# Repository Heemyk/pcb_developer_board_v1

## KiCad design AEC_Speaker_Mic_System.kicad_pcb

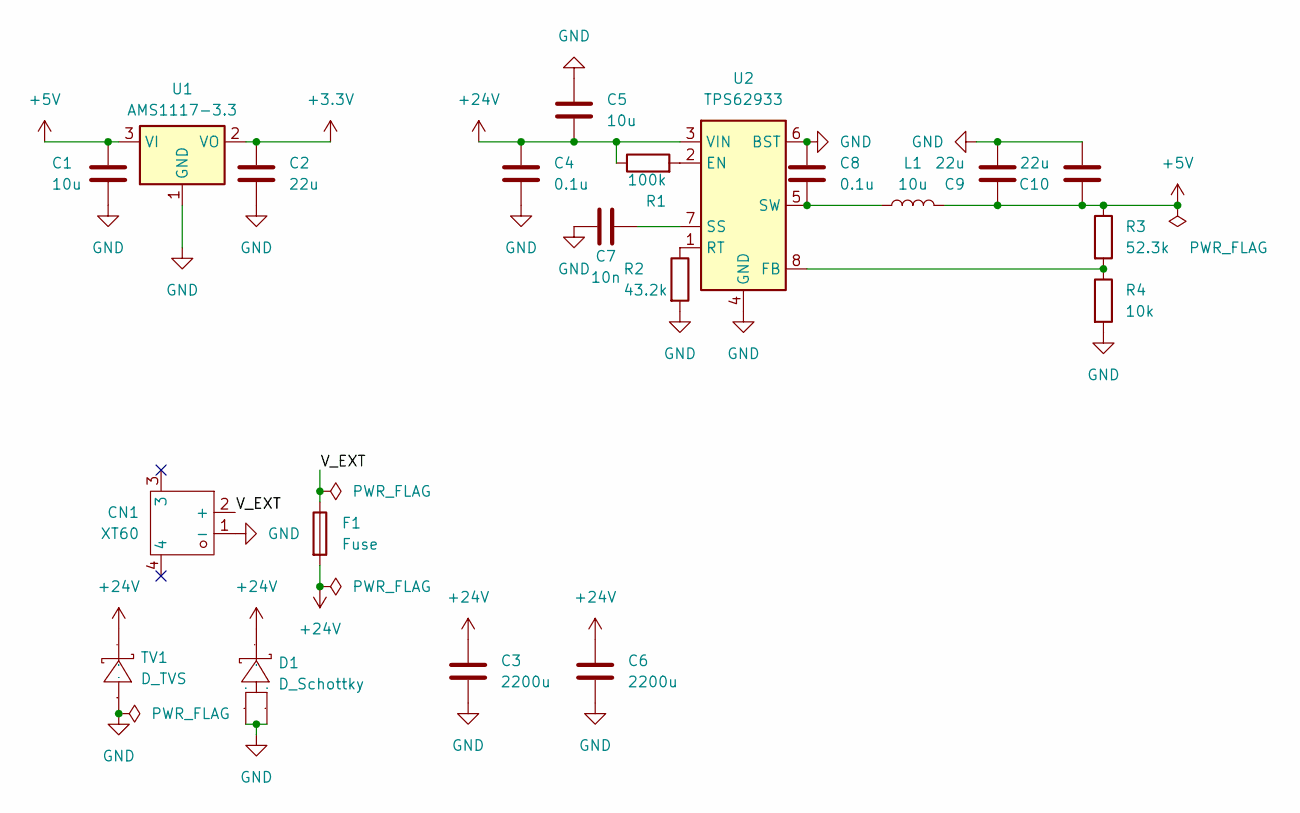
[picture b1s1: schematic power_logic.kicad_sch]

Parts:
C1: 10u; CP_EIA-3216-18_Kemet-A; Voltage Rating 16V; LCSC Part # C7171
C2: 22u; CP_EIA-3216-18_Kemet-A; Voltage Rating 6.6V; LCSC Part # C7183
C3, C6: 2200u; CAP-SMD_BD18.0-L19.0-W19.0-FD_EEEFK1E472SV; LCSC Part # C401728
C4, C8: 0.1u; C_0603_1608Metric; Voltage Rating 50V; LCSC Part # C14633
C5: 10u; C_1210_3225Metric; Voltage Rating 50V; LCSC Part # C116808
C7: 10n; C_0603_1608Metric; Voltage Rating 50V; LCSC Part # C1589
C9, C10: 22u; C_1206_3216Metric; Voltage Rating 25V; LCSC Part # C12891
CN1: XT60; CONN-TH_XT60PW-M; Manufacturer Part XT60PW-M; LCSC Part Name AMASS(艾迈斯)航模插头xt60连接器150公母对接pw锂电池公头 板插卧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
D1: D_Schottky; TO-277_3P-L5.4-W4.0-LS6.5-BR; Manufacturer Part SL1545; LCSC Part Name 电压:45V 电流:15A
F1: Fuse; F1206_32V_12A; LCSC Part # C126815
L1: 10u; IND-SMD_L10.4-W10.3; LCSC Part # C9935
R1: 100k; R_0603_1608Metric
R2: 43.2k; R_0603_1608Metric; LCSC Part # C22356315
R3: 52.3k; R_0603_1608Metric; LCSC Part # C22369875
R4: 10k; R_0603_1608Metric
TV1: D_TVS; Diode_SMC_L7.1-W6.2-LS8.1-R-RD; Manufacturer Part SMCJ28A; LCSC Part Name 单向TVS 28V截止 峰值浪涌电流：33.1A@10/1000us
U1: AMS1117-3.3; SOT-223-3_TabPin2; LCSC Part # C6186
U2: TPS62933; SOT-583-8; LCSC Part # C5219272

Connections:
+3.3V: C2.2, U1.2 (VO); also elsewhere on the board
+5V: C1.2, C9.1, C10.1, L1.2, R3.1, U1.3 (VI); also elsewhere on the board
+24V: C3.1, C4.1, C5.2, C6.1, D1.2 (K), F1.2, R1.1, TV1.2 (K), U2.3 (VIN); also elsewhere on the board
/PCB_Power/V_EXT: CN1.2 (+), F1.1
GND: C1.1, C2.1, C3.2, C4.2, C5.1, C6.2, C7.1, C8.1, C9.2, C10.2, CN1.1 (-), D1.1 (A), D1.3 (A), R2.2, R4.2, TV1.1 (A), U1.1 (GND), U2.4 (GND), U2.6 (BST); also elsewhere on the board
unnamed: R1.2, U2.2 (EN)
unnamed: R3.2, R4.1, U2.8 (FB)
unnamed: R2.1, U2.1 (RT)
unnamed: C7.2, U2.7 (SS)
unnamed: C8.2, L1.1, U2.5 (SW)

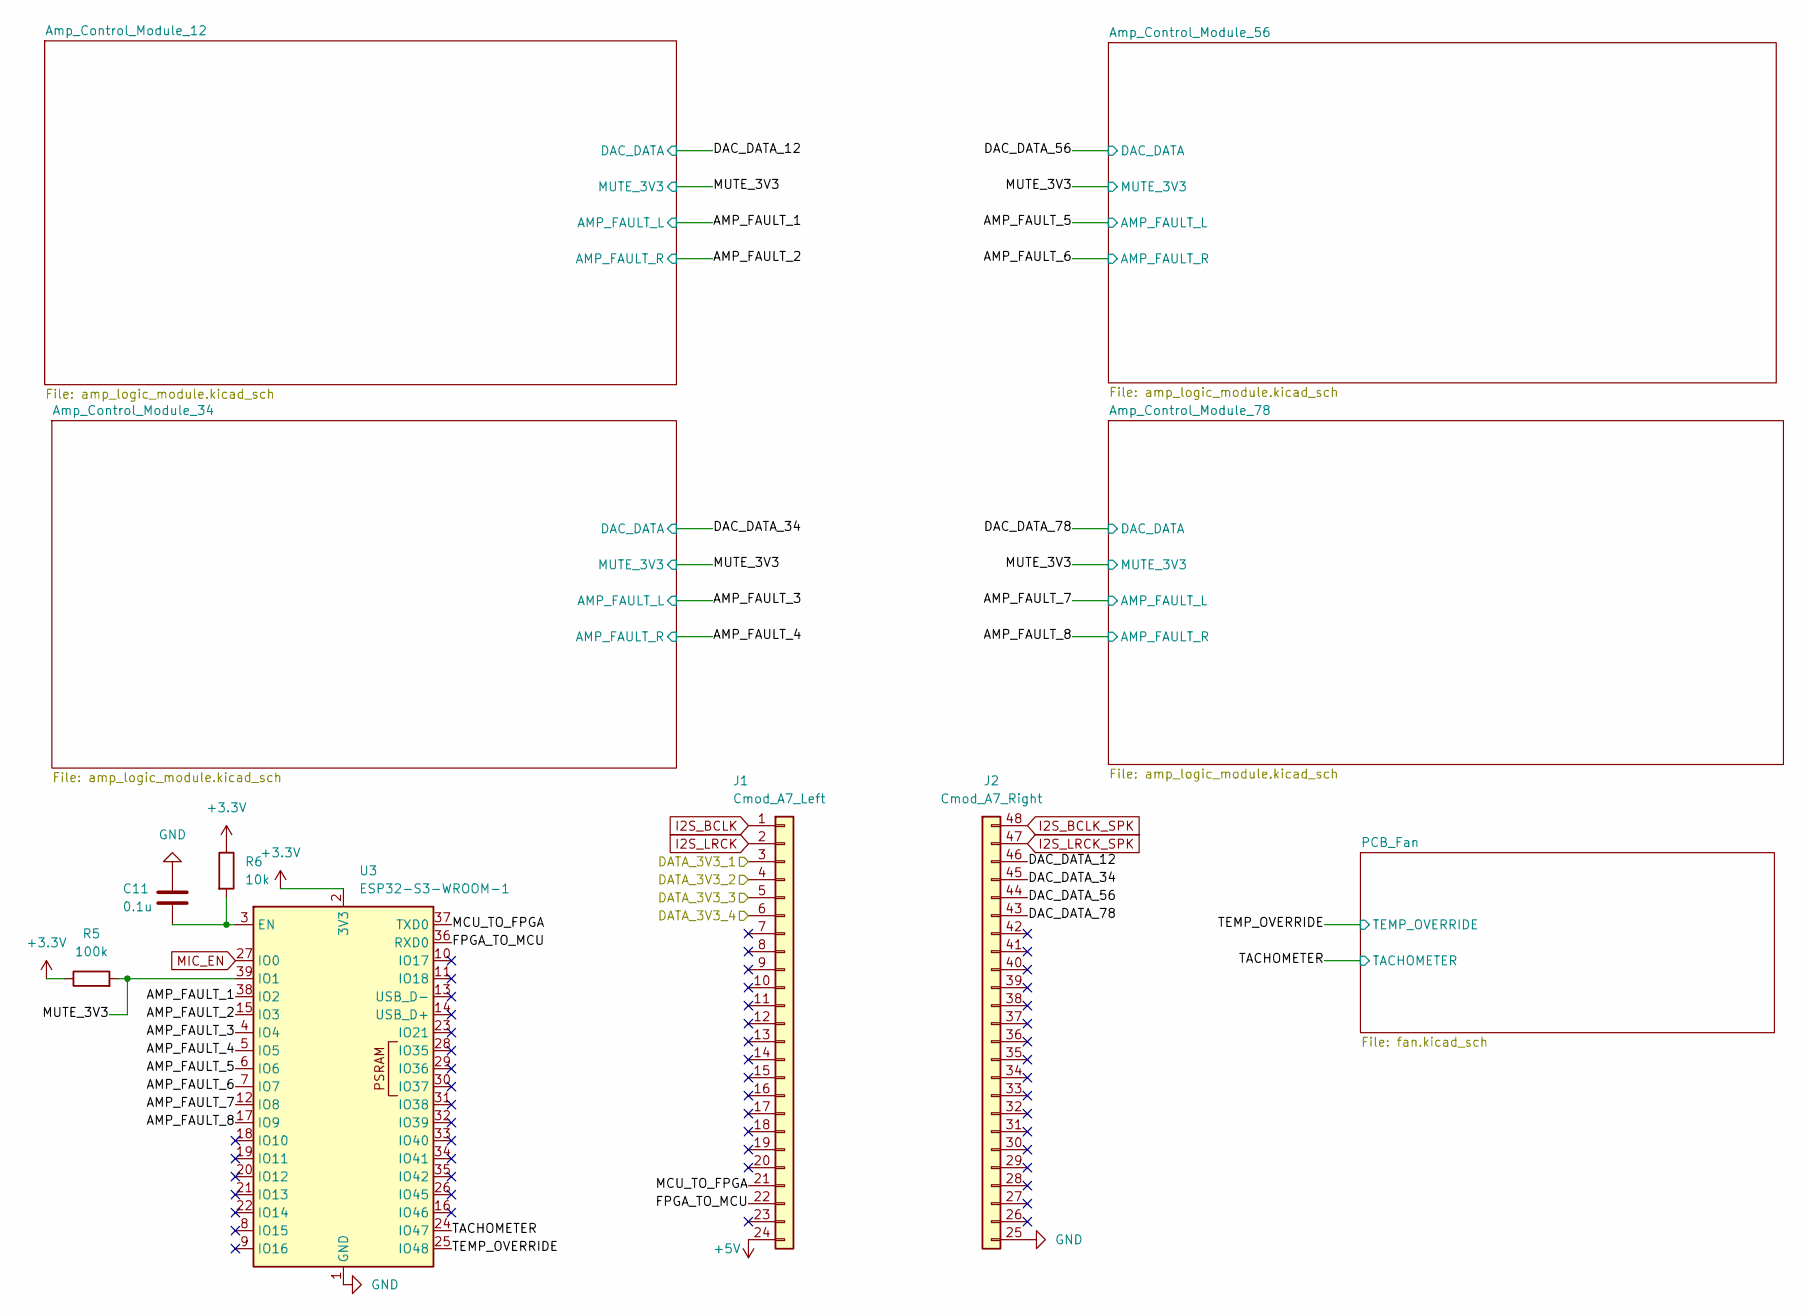
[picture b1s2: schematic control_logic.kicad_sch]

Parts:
C11: 0.1u; C_0603_1608Metric
J1: Cmod_A7_Left; HDR-TH_24P-P2.54-V-F; LCSC Part # C41376163
J2: Cmod_A7_Right; HDR-TH_24P-P2.54-V-F-RIGHT_SIDE_NUMBERING; LCSC Part # C41376163
R5: 100k; R_0603_1608Metric
R6: 10k; R_0603_1608Metric
U3: ESP32-S3-WROOM-1; LCSC Part # C2913202

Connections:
+3.3V: R5.1, R6.1, U3.2 (3V3); also elsewhere on the board
+5V: J1.24; also elsewhere on the board
/Hub_Main/DATA_3V3_1: J1.3; also elsewhere on the board
/Hub_Main/DATA_3V3_2: J1.4; also elsewhere on the board
/Hub_Main/DATA_3V3_3: J1.5; also elsewhere on the board
/Hub_Main/DATA_3V3_4: J1.6; also elsewhere on the board
/PCB_Control/AMP_FAULT_1: U3.38 (IO2); also elsewhere on the board
/PCB_Control/AMP_FAULT_2: U3.15 (IO3); also elsewhere on the board
/PCB_Control/AMP_FAULT_3: U3.4 (IO4); also elsewhere on the board
/PCB_Control/AMP_FAULT_4: U3.5 (IO5); also elsewhere on the board
/PCB_Control/AMP_FAULT_5: U3.6 (IO6); also elsewhere on the board
/PCB_Control/AMP_FAULT_6: U3.7 (IO7); also elsewhere on the board
/PCB_Control/AMP_FAULT_7: U3.12 (IO8); also elsewhere on the board
/PCB_Control/AMP_FAULT_8: U3.17 (IO9); also elsewhere on the board
/PCB_Control/DAC_DATA_12: J2.46 (Pin_22); also elsewhere on the board
/PCB_Control/DAC_DATA_34: J2.45 (Pin_21); also elsewhere on the board
/PCB_Control/DAC_DATA_56: J2.44 (Pin_20); also elsewhere on the board
/PCB_Control/DAC_DATA_78: J2.43 (Pin_19); also elsewhere on the board
/PCB_Control/FPGA_TO_MCU: J1.22, U3.36 (RXD0)
/PCB_Control/MCU_TO_FPGA: J1.21, U3.37 (TXD0)
/PCB_Control/MUTE_3V3: R5.2, U3.39 (IO1); also elsewhere on the board
/PCB_Control/TACHOMETER: U3.24 (IO47); also elsewhere on the board
/PCB_Control/TEMP_OVERRIDE: U3.25 (IO48); also elsewhere on the board
GND: C11.1, J2.25 (Pin_1), U3.1 (GND), U3.40 (GND), U3.41 (GND); also elsewhere on the board
I2S_BCLK: J1.1; also elsewhere on the board
I2S_BCLK_SPK: J2.48 (Pin_24); also elsewhere on the board
I2S_LRCK: J1.2; also elsewhere on the board
I2S_LRCK_SPK: J2.47 (Pin_23); also elsewhere on the board
MIC_EN: U3.27 (IO0); also elsewhere on the board
unnamed: C11.2, R6.2, U3.3 (EN)

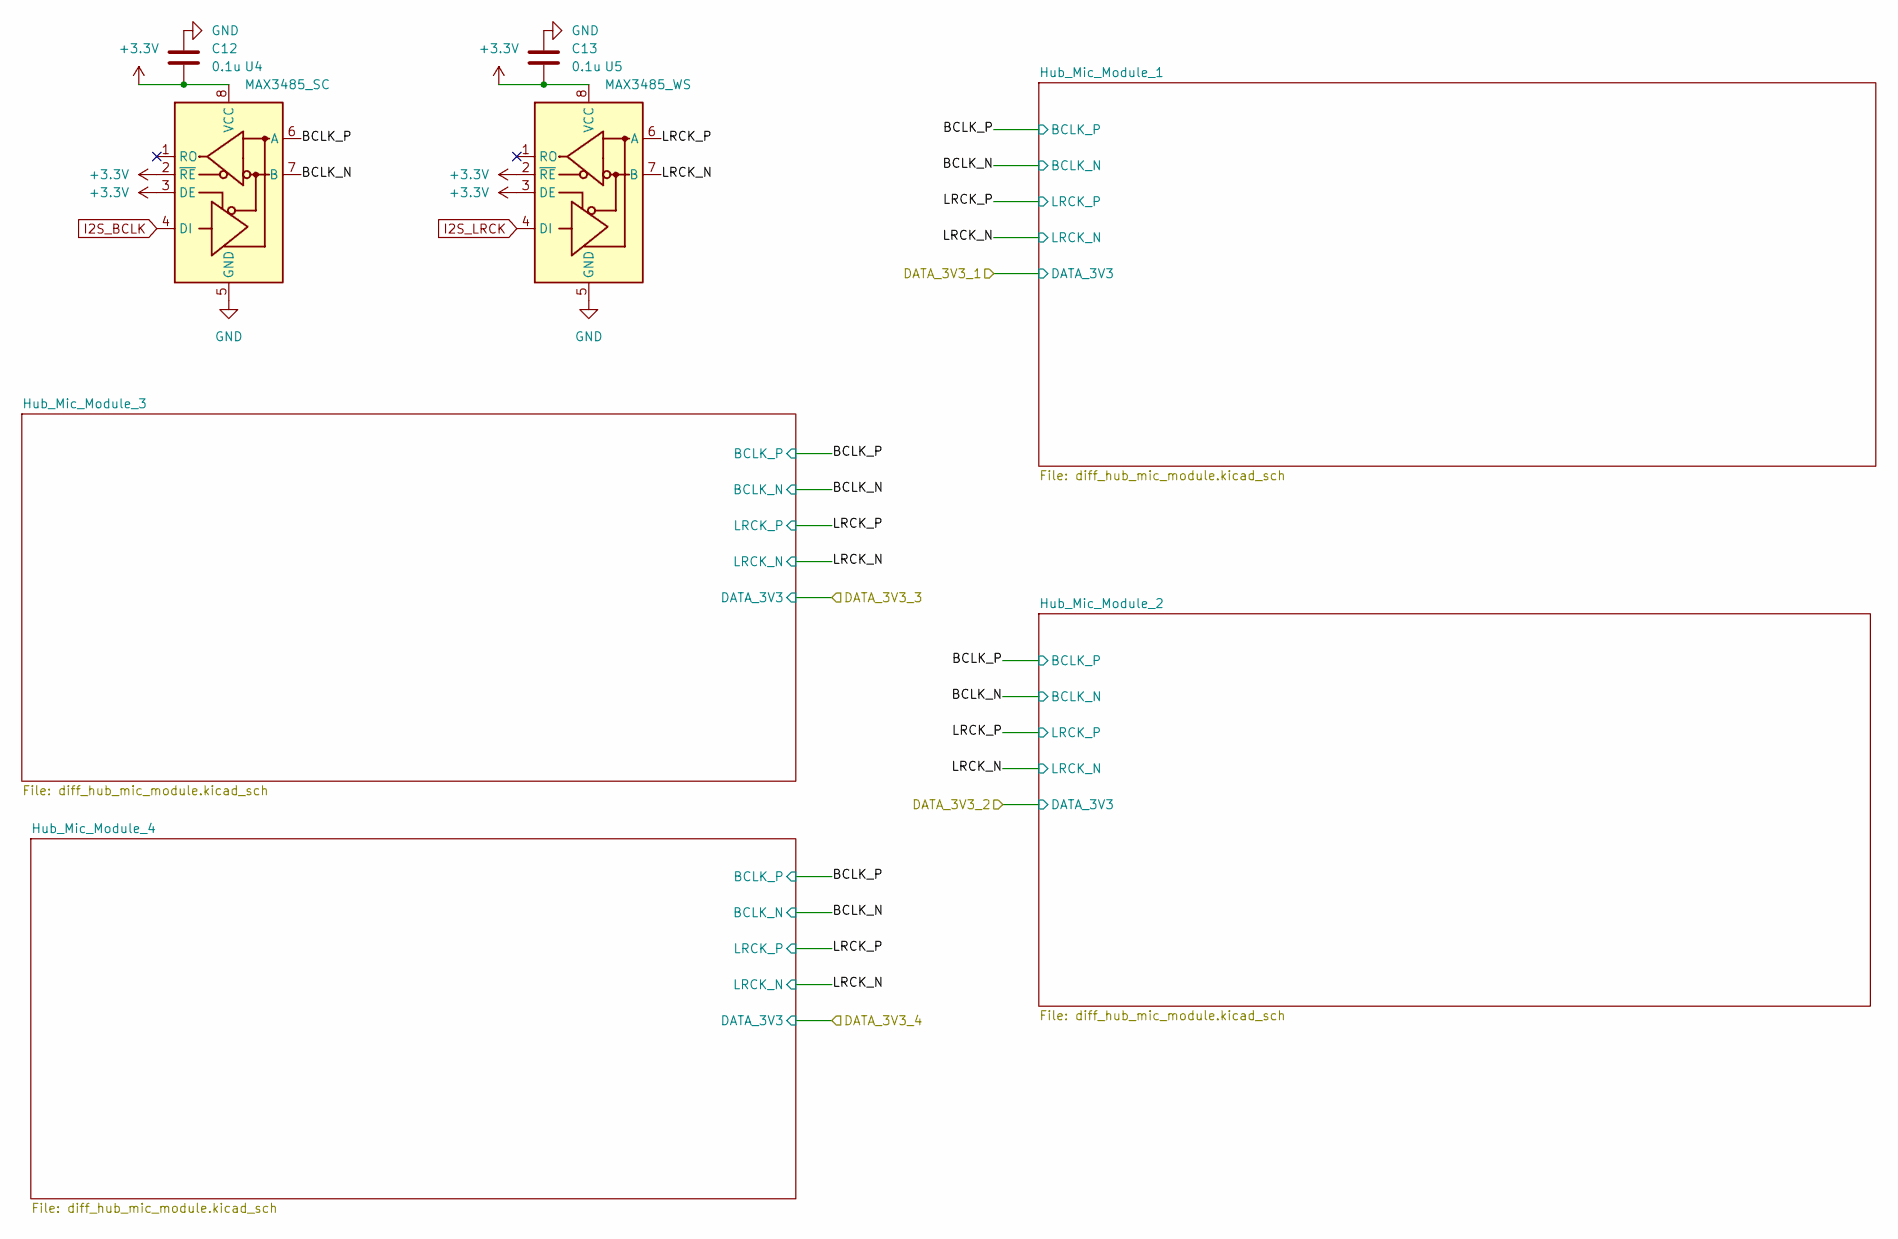
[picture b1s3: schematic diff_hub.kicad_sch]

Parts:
C12, C13: 0.1u; C_0603_1608Metric
U4: MAX3485_SC; SOIC-8_3.9x4.9mm_P1.27mm
U5: MAX3485_WS; SOIC-8_3.9x4.9mm_P1.27mm

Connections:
+3.3V: C12.2, C13.2, U4.2 (~RE), U4.3 (DE), U4.8 (VCC), U5.2 (~RE), U5.3 (DE), U5.8 (VCC); also elsewhere on the board
/Hub_Main/BCLK_N: U4.7 (B); also elsewhere on the board
/Hub_Main/BCLK_P: U4.6 (A); also elsewhere on the board
/Hub_Main/LRCK_N: U5.7 (B); also elsewhere on the board
/Hub_Main/LRCK_P: U5.6 (A); also elsewhere on the board
GND: C12.1, C13.1, U4.5 (GND), U5.5 (GND); also elsewhere on the board
I2S_BCLK: U4.4 (DI); also elsewhere on the board
I2S_LRCK: U5.4 (DI); also elsewhere on the board

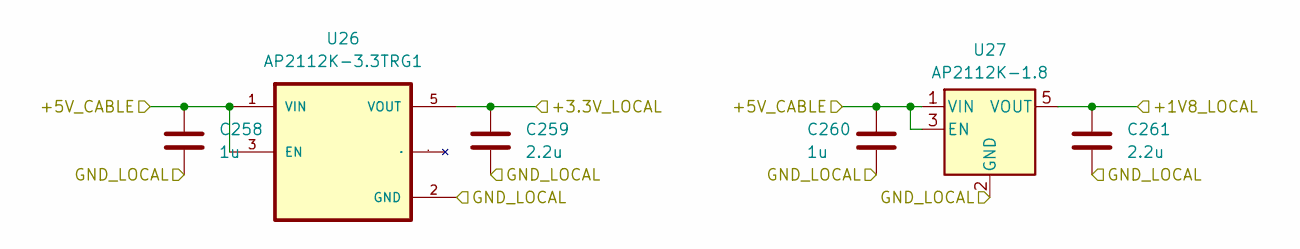
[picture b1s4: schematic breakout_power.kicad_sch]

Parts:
C258: 1u; C_0603_1608Metric; LCSC Part # C15849
C259, C261: 2.2u; C_0603_1608Metric; LCSC Part # C23630
C260: 1u; IND-SMD_L10.4-W10.3; LCSC Part # C15849
U26: AP2112K-3.3TRG1; SOT95P285X140-5N; PARTREV 2-2
U27: AP2112K-1.8; SOT-23-5

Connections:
/Breakout_1/+1V8_LOCAL: C261.2, U27.5 (VOUT); also elsewhere on the board
/Breakout_1/+3.3V_LOCAL: C259.2, U26.5 (VOUT); also elsewhere on the board
/Breakout_1/+5V_CABLE: C258.1, C260.1, U26.1 (VIN), U26.3 (EN), U27.1 (VIN), U27.3 (EN); also elsewhere on the board
/Breakout_1/GND_LOCAL: C258.2, C259.1, C260.2, C261.1, U26.2 (GND), U27.2 (GND); also elsewhere on the board

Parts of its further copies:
C265, C274, C282, C293, C301: 1u; C_0603_1608Metric; LCSC Part # C15849
C266, C268, C275, C277, C283, C285, C294, C296, C302, C304: 2.2u; C_0603_1608Metric; LCSC Part # C23630
C267, C276, C284, C295, C303: 1u; IND-SMD_L10.4-W10.3; LCSC Part # C15849
U29, U40, U47, U55, U62: AP2112K-3.3TRG1; SOT95P285X140-5N; PARTREV 2-2
U30, U41, U48, U56, U63: AP2112K-1.8; SOT-23-5

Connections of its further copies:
/Breakout_2/+1V8_LOCAL: C277.2, U41.5 (VOUT); also elsewhere on the board
/Breakout_2/+3.3V_LOCAL: C275.2, U40.5 (VOUT); also elsewhere on the board
/Breakout_2/+5V_CABLE: C274.1, C276.1, U40.1 (VIN), U40.3 (EN), U41.1 (VIN), U41.3 (EN); also elsewhere on the board
/Breakout_2/GND_LOCAL: C274.2, C275.1, C276.2, C277.1, U40.2 (GND), U41.2 (GND); also elsewhere on the board
/Breakout_3/+1V8_LOCAL: C296.2, U56.5 (VOUT); also elsewhere on the board
/Breakout_3/+3.3V_LOCAL: C294.2, U55.5 (VOUT); also elsewhere on the board
/Breakout_3/+5V_CABLE: C293.1, C295.1, U55.1 (VIN), U55.3 (EN), U56.1 (VIN), U56.3 (EN); also elsewhere on the board
/Breakout_3/GND_LOCAL: C293.2, C294.1, C295.2, C296.1, U55.2 (GND), U56.2 (GND); also elsewhere on the board
/Breakout_4/+1V8_LOCAL: C268.2, U30.5 (VOUT); also elsewhere on the board
/Breakout_4/+3.3V_LOCAL: C266.2, U29.5 (VOUT); also elsewhere on the board
/Breakout_4/+5V_CABLE: C265.1, C267.1, U29.1 (VIN), U29.3 (EN), U30.1 (VIN), U30.3 (EN); also elsewhere on the board
/Breakout_4/GND_LOCAL: C265.2, C266.1, C267.2, C268.1, U29.2 (GND), U30.2 (GND); also elsewhere on the board
/Breakout_5/+1V8_LOCAL: C285.2, U48.5 (VOUT); also elsewhere on the board
/Breakout_5/+3.3V_LOCAL: C283.2, U47.5 (VOUT); also elsewhere on the board
/Breakout_5/+5V_CABLE: C282.1, C284.1, U47.1 (VIN), U47.3 (EN), U48.1 (VIN), U48.3 (EN); also elsewhere on the board
/Breakout_5/GND_LOCAL: C282.2, C283.1, C284.2, C285.1, U47.2 (GND), U48.2 (GND); also elsewhere on the board
/Breakout_6/+1V8_LOCAL: C304.2, U63.5 (VOUT); also elsewhere on the board
/Breakout_6/+3.3V_LOCAL: C302.2, U62.5 (VOUT); also elsewhere on the board
/Breakout_6/+5V_CABLE: C301.1, C303.1, U62.1 (VIN), U62.3 (EN), U63.1 (VIN), U63.3 (EN); also elsewhere on the board
/Breakout_6/GND_LOCAL: C301.2, C302.1, C303.2, C304.1, U62.2 (GND), U63.2 (GND); also elsewhere on the board

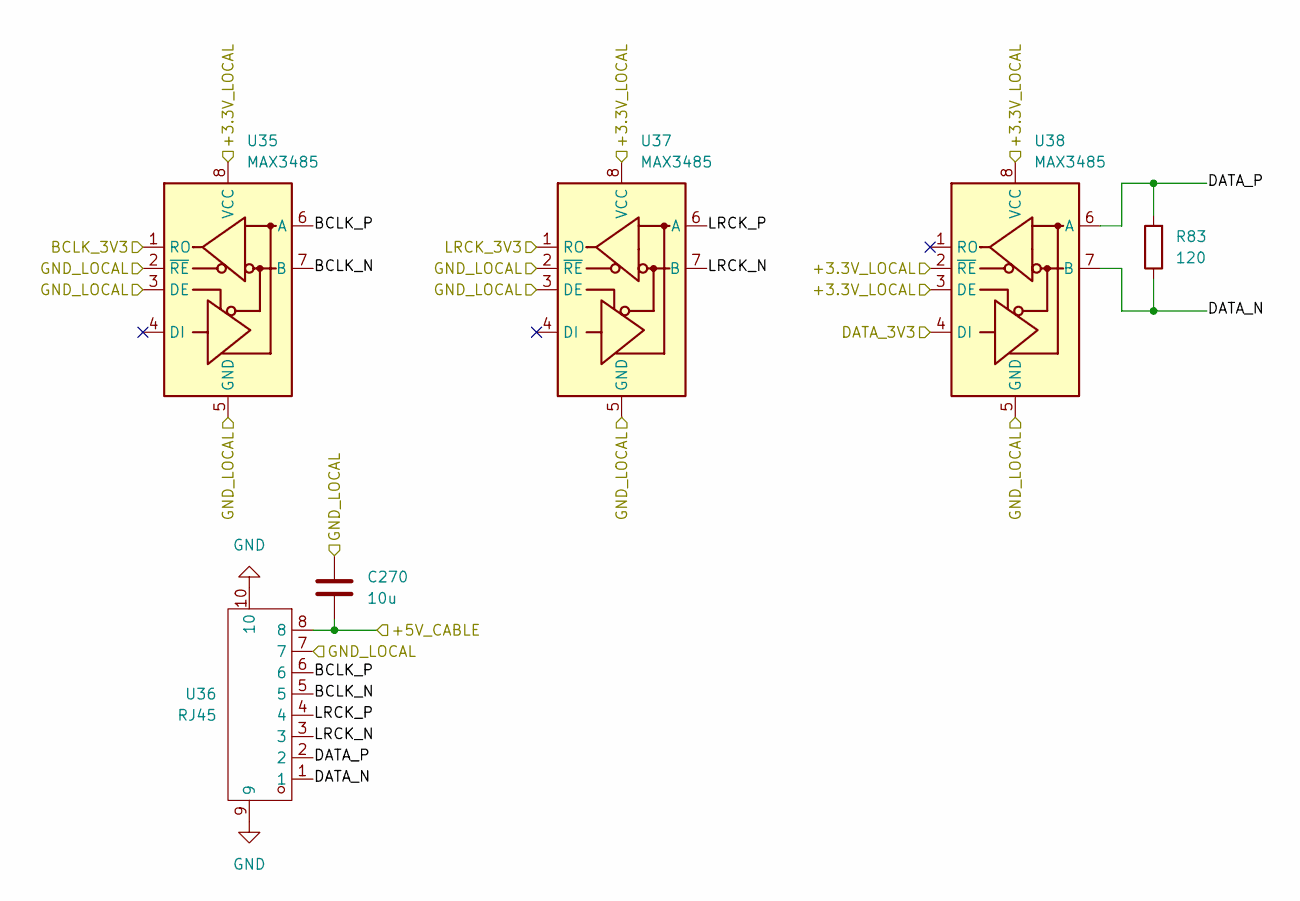
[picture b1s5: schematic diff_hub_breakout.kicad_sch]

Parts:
C270: 10u; C_0603_1608Metric
R83: 120; R_0603_1608Metric
U35, U37, U38: MAX3485; SOIC-8_3.9x4.9mm_P1.27mm
U36: RJ45; RJ45-SMD_HC-RJ45-055-4_2; Manufacturer Part HC-RJ45-055-4; LCSC Part Name 沉板 不带LED

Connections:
/Breakout_1/+3.3V_LOCAL: U35.8 (VCC), U37.8 (VCC), U38.2 (~RE), U38.3 (DE), U38.8 (VCC); also elsewhere on the board
/Breakout_1/+5V_CABLE: C270.2, U36.8; also elsewhere on the board
/Breakout_1/Breakout_Control/BCLK_3V3: U35.1 (RO); also elsewhere on the board
/Breakout_1/Breakout_Control/DATA_3V3: U38.4 (DI); also elsewhere on the board
/Breakout_1/Breakout_Control/WS_3V3: U37.1 (RO); also elsewhere on the board
/Breakout_1/Breakout_Hub/BCLK_N: U35.7 (B), U36.5
/Breakout_1/Breakout_Hub/BCLK_P: U35.6 (A), U36.6
/Breakout_1/Breakout_Hub/DATA_N: R83.1, U36.1, U38.7 (B)
/Breakout_1/Breakout_Hub/DATA_P: R83.2, U36.2, U38.6 (A)
/Breakout_1/Breakout_Hub/LRCK_N: U36.3, U37.7 (B)
/Breakout_1/Breakout_Hub/LRCK_P: U36.4, U37.6 (A)
/Breakout_1/GND_LOCAL: C270.1, U35.2 (~RE), U35.3 (DE), U35.5 (GND), U36.7, U37.2 (~RE), U37.3 (DE), U37.5 (GND), U38.5 (GND); also elsewhere on the board
GND: U36.9, U36.10; also elsewhere on the board

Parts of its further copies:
C269, C278, C286, C297, C305: 10u; C_0603_1608Metric
R81, R85, R88, R93, R101: 120; R_0603_1608Metric
U31, U33, U34, U42, U44, U45, U49, U51, U52, U57, U59, U60, U64, U67, U68: MAX3485; SOIC-8_3.9x4.9mm_P1.27mm
U32, U43, U50, U58, U65: RJ45; RJ45-SMD_HC-RJ45-055-4_2; Manufacturer Part HC-RJ45-055-4; LCSC Part Name 沉板 不带LED

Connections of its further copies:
/Breakout_2/+3.3V_LOCAL: U42.8 (VCC), U44.8 (VCC), U45.2 (~RE), U45.3 (DE), U45.8 (VCC); also elsewhere on the board
/Breakout_2/+5V_CABLE: C278.2, U43.8; also elsewhere on the board
/Breakout_2/Breakout_Control/BCLK_3V3: U42.1 (RO); also elsewhere on the board
/Breakout_2/Breakout_Control/DATA_3V3: U45.4 (DI); also elsewhere on the board
/Breakout_2/Breakout_Control/WS_3V3: U44.1 (RO); also elsewhere on the board
/Breakout_2/Breakout_Hub/BCLK_N: U42.7 (B), U43.5
/Breakout_2/Breakout_Hub/BCLK_P: U42.6 (A), U43.6
/Breakout_2/Breakout_Hub/DATA_N: R85.1, U43.1, U45.7 (B)
/Breakout_2/Breakout_Hub/DATA_P: R85.2, U43.2, U45.6 (A)
/Breakout_2/Breakout_Hub/LRCK_N: U43.3, U44.7 (B)
/Breakout_2/Breakout_Hub/LRCK_P: U43.4, U44.6 (A)
/Breakout_2/GND_LOCAL: C278.1, U42.2 (~RE), U42.3 (DE), U42.5 (GND), U43.7, U44.2 (~RE), U44.3 (DE), U44.5 (GND), U45.5 (GND); also elsewhere on the board
/Breakout_3/+3.3V_LOCAL: U57.8 (VCC), U59.8 (VCC), U60.2 (~RE), U60.3 (DE), U60.8 (VCC); also elsewhere on the board
/Breakout_3/+5V_CABLE: C297.2, U58.8; also elsewhere on the board
/Breakout_3/Breakout_Control/BCLK_3V3: U57.1 (RO); also elsewhere on the board
/Breakout_3/Breakout_Control/DATA_3V3: U60.4 (DI); also elsewhere on the board
/Breakout_3/Breakout_Control/WS_3V3: U59.1 (RO); also elsewhere on the board
/Breakout_3/Breakout_Hub/BCLK_N: U57.7 (B), U58.5
/Breakout_3/Breakout_Hub/BCLK_P: U57.6 (A), U58.6
/Breakout_3/Breakout_Hub/DATA_N: R93.1, U58.1, U60.7 (B)
/Breakout_3/Breakout_Hub/DATA_P: R93.2, U58.2, U60.6 (A)
/Breakout_3/Breakout_Hub/LRCK_N: U58.3, U59.7 (B)
/Breakout_3/Breakout_Hub/LRCK_P: U58.4, U59.6 (A)
/Breakout_3/GND_LOCAL: C297.1, U57.2 (~RE), U57.3 (DE), U57.5 (GND), U58.7, U59.2 (~RE), U59.3 (DE), U59.5 (GND), U60.5 (GND); also elsewhere on the board
/Breakout_4/+3.3V_LOCAL: U31.8 (VCC), U33.8 (VCC), U34.2 (~RE), U34.3 (DE), U34.8 (VCC); also elsewhere on the board
/Breakout_4/+5V_CABLE: C269.2, U32.8; also elsewhere on the board
/Breakout_4/Breakout_Control/BCLK_3V3: U31.1 (RO); also elsewhere on the board
/Breakout_4/Breakout_Control/DATA_3V3: U34.4 (DI); also elsewhere on the board
/Breakout_4/Breakout_Control/WS_3V3: U33.1 (RO); also elsewhere on the board
/Breakout_4/Breakout_Hub/BCLK_N: U31.7 (B), U32.5
/Breakout_4/Breakout_Hub/BCLK_P: U31.6 (A), U32.6
/Breakout_4/Breakout_Hub/DATA_N: R81.1, U32.1, U34.7 (B)
/Breakout_4/Breakout_Hub/DATA_P: R81.2, U32.2, U34.6 (A)
/Breakout_4/Breakout_Hub/LRCK_N: U32.3, U33.7 (B)
/Breakout_4/Breakout_Hub/LRCK_P: U32.4, U33.6 (A)
/Breakout_4/GND_LOCAL: C269.1, U31.2 (~RE), U31.3 (DE), U31.5 (GND), U32.7, U33.2 (~RE), U33.3 (DE), U33.5 (GND), U34.5 (GND); also elsewhere on the board
/Breakout_5/+3.3V_LOCAL: U49.8 (VCC), U51.8 (VCC), U52.2 (~RE), U52.3 (DE), U52.8 (VCC); also elsewhere on the board
/Breakout_5/+5V_CABLE: C286.2, U50.8; also elsewhere on the board
/Breakout_5/Breakout_Control/BCLK_3V3: U49.1 (RO); also elsewhere on the board
/Breakout_5/Breakout_Control/DATA_3V3: U52.4 (DI); also elsewhere on the board
/Breakout_5/Breakout_Control/WS_3V3: U51.1 (RO); also elsewhere on the board
/Breakout_5/Breakout_Hub/BCLK_N: U49.7 (B), U50.5
/Breakout_5/Breakout_Hub/BCLK_P: U49.6 (A), U50.6
/Breakout_5/Breakout_Hub/DATA_N: R88.1, U50.1, U52.7 (B)
/Breakout_5/Breakout_Hub/DATA_P: R88.2, U50.2, U52.6 (A)
/Breakout_5/Breakout_Hub/LRCK_N: U50.3, U51.7 (B)
/Breakout_5/Breakout_Hub/LRCK_P: U50.4, U51.6 (A)
/Breakout_5/GND_LOCAL: C286.1, U49.2 (~RE), U49.3 (DE), U49.5 (GND), U50.7, U51.2 (~RE), U51.3 (DE), U51.5 (GND), U52.5 (GND); also elsewhere on the board
/Breakout_6/+3.3V_LOCAL: U64.8 (VCC), U67.8 (VCC), U68.2 (~RE), U68.3 (DE), U68.8 (VCC); also elsewhere on the board
/Breakout_6/+5V_CABLE: C305.2, U65.8; also elsewhere on the board
/Breakout_6/Breakout_Control/BCLK_3V3: U64.1 (RO); also elsewhere on the board
/Breakout_6/Breakout_Control/DATA_3V3: U68.4 (DI); also elsewhere on the board
/Breakout_6/Breakout_Control/WS_3V3: U67.1 (RO); also elsewhere on the board
/Breakout_6/Breakout_Hub/BCLK_N: U64.7 (B), U65.5
/Breakout_6/Breakout_Hub/BCLK_P: U64.6 (A), U65.6
/Breakout_6/Breakout_Hub/DATA_N: R101.1, U65.1, U68.7 (B)
/Breakout_6/Breakout_Hub/DATA_P: R101.2, U65.2, U68.6 (A)
/Breakout_6/Breakout_Hub/LRCK_N: U65.3, U67.7 (B)
/Breakout_6/Breakout_Hub/LRCK_P: U65.4, U67.6 (A)
/Breakout_6/GND_LOCAL: C305.1, U64.2 (~RE), U64.3 (DE), U64.5 (GND), U65.7, U67.2 (~RE), U67.3 (DE), U67.5 (GND), U68.5 (GND); also elsewhere on the board
GND: U32.9, U32.10, U43.9, U43.10, U50.9, U50.10, U58.9, U58.10, U65.9, U65.10; also elsewhere on the board

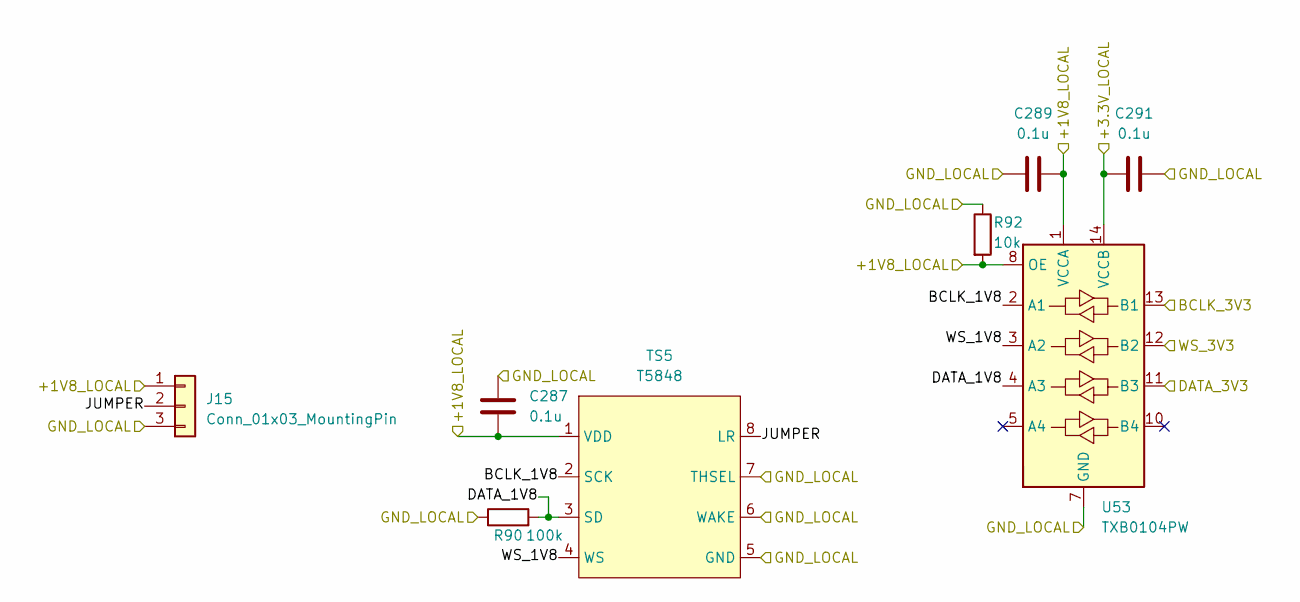
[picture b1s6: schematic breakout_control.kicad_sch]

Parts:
C287, C289, C291: 0.1u; C_0603_1608Metric
J15: Conn_01x03_MountingPin; PinHeader_1x03_P2.54mm_Vertical_SMD_Pin1Left; LCSC Part # C5160786
R90: 100k; R_0603_1608Metric
R92: 10k; R_0603_1608Metric
TS5: T5848; TDK_T5848_Pad
U53: TXB0104PW; TSSOP-14_4.4x5mm_P0.65mm

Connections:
/Breakout_1/+1V8_LOCAL: C287.1, C289.2, J15.1, R92.2, TS5.1 (VDD), U53.1 (VCCA), U53.8 (OE); also elsewhere on the board
/Breakout_1/+3.3V_LOCAL: C291.1, U53.14 (VCCB); also elsewhere on the board
/Breakout_1/Breakout_Control/BCLK_1V8: TS5.2 (SCK), U53.2 (A1)
/Breakout_1/Breakout_Control/BCLK_3V3: U53.13 (B1); also elsewhere on the board
/Breakout_1/Breakout_Control/DATA_1V8: R90.2, TS5.3 (SD), U53.4 (A3)
/Breakout_1/Breakout_Control/DATA_3V3: U53.11 (B3); also elsewhere on the board
/Breakout_1/Breakout_Control/JUMPER: J15.2, TS5.8 (LR)
/Breakout_1/Breakout_Control/WS_1V8: TS5.4 (WS), U53.3 (A2)
/Breakout_1/Breakout_Control/WS_3V3: U53.12 (B2); also elsewhere on the board
/Breakout_1/GND_LOCAL: C287.2, C289.1, C291.2, J15.3, R90.1, R92.1, TS5.5 (GND), TS5.6 (WAKE), TS5.7 (THSEL), U53.7 (GND); also elsewhere on the board

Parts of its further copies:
C262, C263, C264, C271, C272, C273, C279, C280, C281, C288, C290, C292, C298, C299, C300: 0.1u; C_0603_1608Metric
J11, J12, J13, J14, J16: Conn_01x03_MountingPin; PinHeader_1x03_P2.54mm_Vertical_SMD_Pin1Left; LCSC Part # C5160786
R79, R82, R86, R89, R94: 100k; R_0603_1608Metric
R80, R84, R87, R91, R95: 10k; R_0603_1608Metric
TS1, TS2, TS3, TS4, TS6: T5848; TDK_T5848_Pad
U28, U39, U46, U54, U61: TXB0104PW; TSSOP-14_4.4x5mm_P0.65mm

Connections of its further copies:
/Breakout_2/+1V8_LOCAL: C271.1, C272.2, J12.1, R84.2, TS2.1 (VDD), U39.1 (VCCA), U39.8 (OE); also elsewhere on the board
/Breakout_2/+3.3V_LOCAL: C273.1, U39.14 (VCCB); also elsewhere on the board
/Breakout_2/Breakout_Control/BCLK_1V8: TS2.2 (SCK), U39.2 (A1)
/Breakout_2/Breakout_Control/BCLK_3V3: U39.13 (B1); also elsewhere on the board
/Breakout_2/Breakout_Control/DATA_1V8: R82.2, TS2.3 (SD), U39.4 (A3)
/Breakout_2/Breakout_Control/DATA_3V3: U39.11 (B3); also elsewhere on the board
/Breakout_2/Breakout_Control/JUMPER: J12.2, TS2.8 (LR)
/Breakout_2/Breakout_Control/WS_1V8: TS2.4 (WS), U39.3 (A2)
/Breakout_2/Breakout_Control/WS_3V3: U39.12 (B2); also elsewhere on the board
/Breakout_2/GND_LOCAL: C271.2, C272.1, C273.2, J12.3, R82.1, R84.1, TS2.5 (GND), TS2.6 (WAKE), TS2.7 (THSEL), U39.7 (GND); also elsewhere on the board
/Breakout_3/+1V8_LOCAL: C288.1, C290.2, J14.1, R91.2, TS4.1 (VDD), U54.1 (VCCA), U54.8 (OE); also elsewhere on the board
/Breakout_3/+3.3V_LOCAL: C292.1, U54.14 (VCCB); also elsewhere on the board
/Breakout_3/Breakout_Control/BCLK_1V8: TS4.2 (SCK), U54.2 (A1)
/Breakout_3/Breakout_Control/BCLK_3V3: U54.13 (B1); also elsewhere on the board
/Breakout_3/Breakout_Control/DATA_1V8: R89.2, TS4.3 (SD), U54.4 (A3)
/Breakout_3/Breakout_Control/DATA_3V3: U54.11 (B3); also elsewhere on the board
/Breakout_3/Breakout_Control/JUMPER: J14.2, TS4.8 (LR)
/Breakout_3/Breakout_Control/WS_1V8: TS4.4 (WS), U54.3 (A2)
/Breakout_3/Breakout_Control/WS_3V3: U54.12 (B2); also elsewhere on the board
/Breakout_3/GND_LOCAL: C288.2, C290.1, C292.2, J14.3, R89.1, R91.1, TS4.5 (GND), TS4.6 (WAKE), TS4.7 (THSEL), U54.7 (GND); also elsewhere on the board
/Breakout_4/+1V8_LOCAL: C262.1, C263.2, J11.1, R80.2, TS1.1 (VDD), U28.1 (VCCA), U28.8 (OE); also elsewhere on the board
/Breakout_4/+3.3V_LOCAL: C264.1, U28.14 (VCCB); also elsewhere on the board
/Breakout_4/Breakout_Control/BCLK_1V8: TS1.2 (SCK), U28.2 (A1)
/Breakout_4/Breakout_Control/BCLK_3V3: U28.13 (B1); also elsewhere on the board
/Breakout_4/Breakout_Control/DATA_1V8: R79.2, TS1.3 (SD), U28.4 (A3)
/Breakout_4/Breakout_Control/DATA_3V3: U28.11 (B3); also elsewhere on the board
/Breakout_4/Breakout_Control/JUMPER: J11.2, TS1.8 (LR)
/Breakout_4/Breakout_Control/WS_1V8: TS1.4 (WS), U28.3 (A2)
/Breakout_4/Breakout_Control/WS_3V3: U28.12 (B2); also elsewhere on the board
/Breakout_4/GND_LOCAL: C262.2, C263.1, C264.2, J11.3, R79.1, R80.1, TS1.5 (GND), TS1.6 (WAKE), TS1.7 (THSEL), U28.7 (GND); also elsewhere on the board
/Breakout_5/+1V8_LOCAL: C279.1, C280.2, J13.1, R87.2, TS3.1 (VDD), U46.1 (VCCA), U46.8 (OE); also elsewhere on the board
/Breakout_5/+3.3V_LOCAL: C281.1, U46.14 (VCCB); also elsewhere on the board
/Breakout_5/Breakout_Control/BCLK_1V8: TS3.2 (SCK), U46.2 (A1)
/Breakout_5/Breakout_Control/BCLK_3V3: U46.13 (B1); also elsewhere on the board
/Breakout_5/Breakout_Control/DATA_1V8: R86.2, TS3.3 (SD), U46.4 (A3)
/Breakout_5/Breakout_Control/DATA_3V3: U46.11 (B3); also elsewhere on the board
/Breakout_5/Breakout_Control/JUMPER: J13.2, TS3.8 (LR)
/Breakout_5/Breakout_Control/WS_1V8: TS3.4 (WS), U46.3 (A2)
/Breakout_5/Breakout_Control/WS_3V3: U46.12 (B2); also elsewhere on the board
/Breakout_5/GND_LOCAL: C279.2, C280.1, C281.2, J13.3, R86.1, R87.1, TS3.5 (GND), TS3.6 (WAKE), TS3.7 (THSEL), U46.7 (GND); also elsewhere on the board
/Breakout_6/+1V8_LOCAL: C298.1, C299.2, J16.1, R95.2, TS6.1 (VDD), U61.1 (VCCA), U61.8 (OE); also elsewhere on the board
/Breakout_6/+3.3V_LOCAL: C300.1, U61.14 (VCCB); also elsewhere on the board
/Breakout_6/Breakout_Control/BCLK_1V8: TS6.2 (SCK), U61.2 (A1)
/Breakout_6/Breakout_Control/BCLK_3V3: U61.13 (B1); also elsewhere on the board
/Breakout_6/Breakout_Control/DATA_1V8: R94.2, TS6.3 (SD), U61.4 (A3)
/Breakout_6/Breakout_Control/DATA_3V3: U61.11 (B3); also elsewhere on the board
/Breakout_6/Breakout_Control/JUMPER: J16.2, TS6.8 (LR)
/Breakout_6/Breakout_Control/WS_1V8: TS6.4 (WS), U61.3 (A2)
/Breakout_6/Breakout_Control/WS_3V3: U61.12 (B2); also elsewhere on the board
/Breakout_6/GND_LOCAL: C298.2, C299.1, C300.2, J16.3, R94.1, R95.1, TS6.5 (GND), TS6.6 (WAKE), TS6.7 (THSEL), U61.7 (GND); also elsewhere on the board

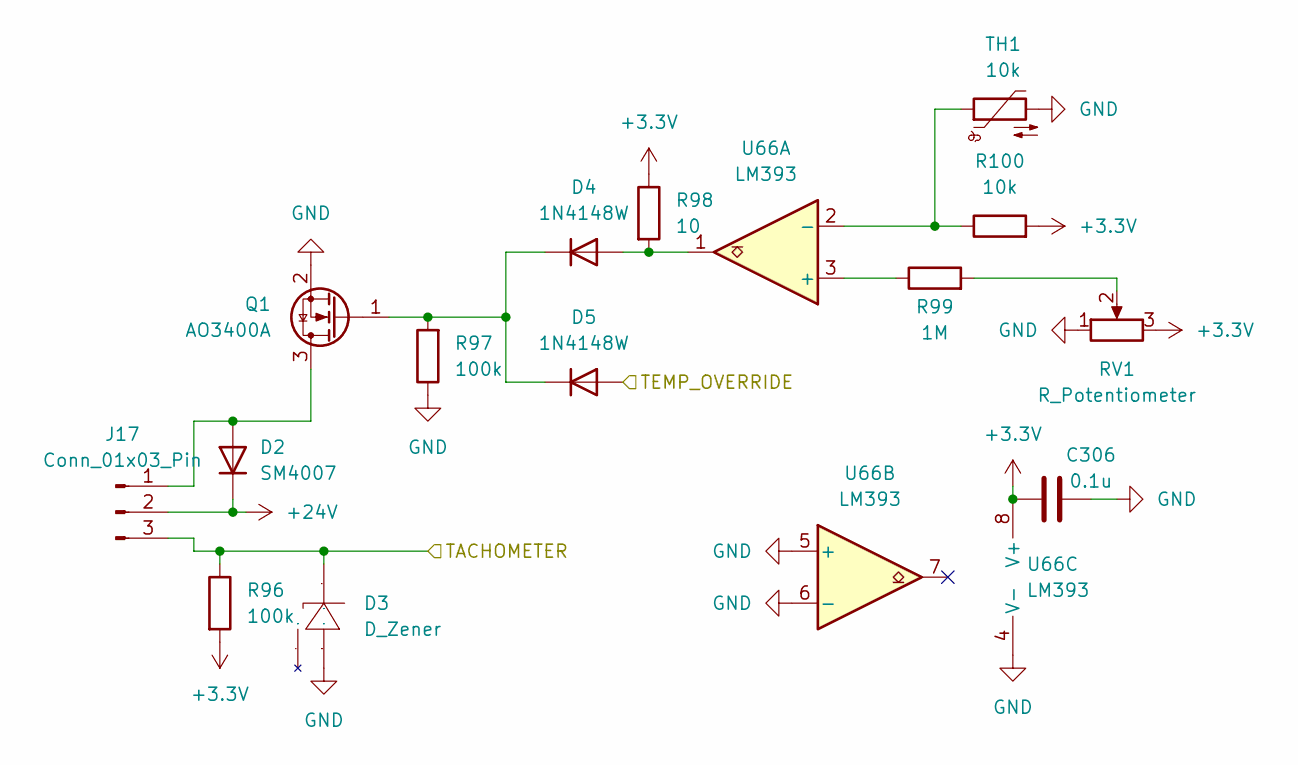
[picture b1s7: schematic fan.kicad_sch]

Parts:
C306: 0.1u; C_0603_1608Metric
D2: SM4007; D_MELF
D3: D_Zener; Zener_SOT-23_L2.9-W1.3-P1.90-LS2.4-BR; Manufacturer Part BZX84-C3V3,215; LCSC Part Name BZX84-C3V3,215
D4, D5: 1N4148W; D_SOD-123
J17: Conn_01x03_Pin; Molex_KK-254_AE-6410-03A_1x03_P2.54mm_Vertical; LCSC Part # C5333416
Q1: AO3400A; SOT-23
R96, R97: 100k; R_0603_1608Metric
R98: 10; R_0805_2012Metric
R99: 1M; R_0603_1608Metric
R100: 10k; R_0603_1608Metric
RV1: R_Potentiometer; RES-ADJ-TH_3362P; LCSC Part # C58159
TH1: 10k; R_0603_1608Metric; LCSC Part # C5385
U66: LM393; SOIC-8_3.9x4.9mm_P1.27mm; LCSC Part # C32901

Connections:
+3.3V: C306.1, R96.2, R98.1, R100.2, RV1.3, U66.8 (V+); also elsewhere on the board
+24V: D2.1 (K), J17.2; also elsewhere on the board
/PCB_Control/TACHOMETER: D3.3 (K), J17.3, R96.1; also elsewhere on the board
/PCB_Control/TEMP_OVERRIDE: D5.2 (A); also elsewhere on the board
GND: C306.2, D3.1 (A), Q1.2 (S), R97.1, RV1.1, TH1.2, U66.4 (V-), U66.5 (+), U66.6 (-); also elsewhere on the board
unnamed: D2.2 (A), J17.1, Q1.3 (D)
unnamed: D4.2 (A), R98.2, U66.1
unnamed: D4.1 (K), D5.1 (K), Q1.1 (G), R97.2
unnamed: R99.2, RV1.2
unnamed: R99.1, U66.3 (+)
unnamed: R100.1, TH1.1, U66.2 (-)
